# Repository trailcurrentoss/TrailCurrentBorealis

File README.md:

# TrailCurrent Borealis

Environmental and safety sensor node for toy haulers, RVs, and similar enclosed living spaces. Measures temperature, humidity, real CO2, VOC index, carbon monoxide, and propane / LPG levels, then broadcasts readings over a CAN bus. Supports over-the-air (OTA) firmware updates, WiFi credential provisioning via CAN, and network discovery for integration with TrailCurrent Headwaters.

## Hardware

- **MCU board:** [Waveshare ESP32-S3-RS485-CAN](https://www.waveshare.com/esp32-s3-rs485-can.htm)
  - ESP32-S3R8 (8MB PSRAM, external 16MB flash)
  - Built-in isolated CAN transceiver (TJA1051) on GPIO15/16
  - Built-in isolated RS485 transceiver (unused by Borealis)
  - External PCF85063AT RTC
  - 7-36V DC input or 5V USB-C
- **CO2 / temp / humidity:** DFRobot SEN0536 (Sensirion SCD41, photoacoustic NDIR)
- **VOC trending:** DFRobot SEN0394 (Sensirion SGP40, VOC Index 1-500)
- **Carbon monoxide:** DFRobot SEN0466 (factory-calibrated electrochemical, 0-1000 ppm)
- **Propane / LPG:** DFRobot SEN0131 (MQ-6 with adjustable potentiometer)

### Pin Assignments

| GPIO | Function |
|------|----------|
| 5 | I2C SDA (SCD41, SGP40, SEN0466) |
| 6 | I2C SCL (SCD41, SGP40, SEN0466) |
| 3 | MQ-6 analog input (ADC1_CH2, via 10k/15k divider) |
| 15 | CAN TX (internal transceiver) |
| 16 | CAN RX (internal transceiver) |

See [`DOCS/sensor-wiring.md`](DOCS/sensor-wiring.md) for full wiring details and the [ribbon-cable diagram](DOCS/borealis-ribbon-cable.svg). When the parts arrive, work through [`DOCS/arrival-todos.md`](DOCS/arrival-todos.md) for the assembly, calibration, and validation checklist.

### Circuit Notes

- KiCad schematic and PCB files are in the `EDA/` directory
- The MQ-6 sensor's analog output swings 0-5V; a 10kΩ + 15kΩ resistor divider scales it to 0-3V at the ADC pin
- Add a 100nF cap from the ADC pin to GND for noise filtering near the heater

## Building

This project uses [ESP-IDF](https://docs.espressif.com/projects/esp-idf/en/stable/esp32s3/get-started/index.html) (v5.x).

```bash
# Configure (first time only)
idf.py set-target esp32s3

# Build
idf.py build

# Flash via USB
idf.py flash

# Monitor serial output
idf.py monitor

# Build, flash, and monitor in one step
idf.py build flash monitor
```

### OTA Upload

```bash
curl -X POST http://<hostname>.local/ota --data-binary @build/borealis.bin
```

## Architecture

| File | Purpose |
|------|---------|
| `main/main.c` | Sensor reading loop, TWAI task, CAN frame transmission |
| `main/sensors.c/h` | I²C drivers for SCD41, SGP40, SEN0466; ADC reading and Rs/R0 calculation for MQ-6 |
| `main/wifi_config.c/h` | NVS-backed WiFi credentials and STA connect/disconnect |
| `main/ota.c/h` | HTTP POST `/ota` server, runs in dedicated task |
| `main/discovery.c/h` | mDNS-based network discovery for Headwaters registration |

### CAN Bus Task

The TWAI (CAN) driver runs in a dedicated FreeRTOS task with alert-based message handling. It uses a dual-state transmission model:

- **TX_ACTIVE** (1000 ms period): Normal operation when peers are detected on the bus
- **TX_PROBING** (2000 ms period): Slow probe when no peers are ACKing, reduces bus noise

The task automatically transitions between states based on TX success/failure and incoming messages. Bus-off recovery is handled via TWAI alerts. This pattern is shared with all other TrailCurrent ESP-IDF modules — see `TrailCurrentReservoir`, `TrailCurrentSwitchback`, etc.

## CAN Bus Protocol

All communication uses a 500 kbps CAN bus. The device transmits sensor data and receives OTA / WiFi / discovery commands.

### Environmental Data (TX)

**CAN ID:** `0x1F` | **DLC:** 8 | **Period:** 1000 ms

| Byte | Content |
|------|---------|
| 0 | Temperature (°C, signed int8, rounded) |
| 1 | Temperature (°F, signed int8, rounded) |
| 2-3 | Humidity (big-endian uint16, value × 100, e.g. 4523 = 45.23%) |
| 4-5 | Real CO2 in ppm (big-endian uint16, NDIR measurement from SCD41) |
| 6-7 | VOC Index (big-endian uint16, range 1-500, baseline ≈ 100) |

### Safety Data (TX)

**CAN ID:** `0x20` | **DLC:** 8 | **Period:** 1000 ms

| Byte | Content |
|------|---------|
| 0-1 | CO concentration in ppm (big-endian uint16) |
| 2-3 | LPG / propane Rs/R0 ratio × 1000 (big-endian uint16; lower = more gas) |
| 4 | Alarm flags (bitmask) |
| 5-7 | Reserved |

Alarm flag bits:
- `0x01` CO warning (≥ 70 ppm)
- `0x02` CO alarm (≥ 200 ppm)
- `0x04` LPG warning (Rs/R0 < 0.5)
- `0x08` LPG alarm (Rs/R0 < 0.3)
- `0x10` CO2 warning (≥ 1500 ppm)
- `0x20` CO2 alarm (≥ 2500 ppm)
- `0x40` VOC alarm (Index ≥ 400)

### OTA Trigger (RX)

**CAN ID:** `0x00` | **DLC:** 3+

| Byte | Content |
|------|---------|
| 0-2 | Target MAC suffix (e.g., `F2 7E 6C` for hostname `esp32-F27E6C`) |

When the MAC matches, the device connects to its configured WiFi network, starts an HTTP server at `/ota`, and waits for a firmware upload for 3 minutes before returning to normal operation.

### WiFi Configuration (RX)

**CAN ID:** `0x01` | **DLC:** varies

WiFi credentials are provisioned over CAN using a chunked protocol. Credentials are stored in NVS (non-volatile storage) and persist across reboots.

| Byte 0 | Message Type |
|--------|-------------|
| `0x01` | Start: contains SSID length, password length, chunk counts |
| `0x02` | SSID chunk: 6-byte payload with chunk index |
| `0x03` | Password chunk: 6-byte payload with chunk index |
| `0x04` | End: contains XOR checksum for validation |

The protocol includes a 5-second timeout — if chunks stop arriving, the state resets.

### Discovery Trigger (RX)

**CAN ID:** `0x02` | **DLC:** any (broadcast)

When received, the device connects to WiFi and advertises itself via mDNS (`_trailcurrent._tcp`) with TXT records:

| Key | Value |
|-----|-------|
| `type` | `borealis` |
| `canid` | `0x1F` |
| `fw` | firmware version |

Headwaters confirms registration by calling `GET /discovery/confirm`. The discovery window is 3 minutes.

### Firmware Version Report (TX)

**CAN ID:** `0x04` | **DLC:** 6

Sent once on boot after CAN initialization, then again whenever a peer is first detected. Reports the running firmware version so Headwaters can track what each device is running.

| Byte | Content |
|------|---------|
| 0-2 | Last 3 bytes of device WiFi MAC (matches hostname `esp32-XXYYZZ`) |
| 3 | Version major |
| 4 | Version minor |
| 5 | Version patch |

## Air Quality and Safety Thresholds

### Real CO2 (SCD41, NDIR)

| ppm | Level |
|-----|-------|
| < 800 | Fresh / well-ventilated |
| 800-1499 | Normal indoor |
| 1500-2499 | Stuffy / drowsiness possible |
| ≥ 2500 | Alarm |

### VOC Index (SGP40)

| Index | Meaning |
|-------|---------|
| 1-99 | Better than recent baseline |
| 100 | Typical indoor air (24-hour running average) |
| 101-249 | Worse than baseline |
| 250-399 | Significant pollution event |
| 400-500 | Severe pollution event |

### Carbon Monoxide (SEN0466)

| ppm | Level |
|-----|-------|
| < 35 | Normal |
| 35-69 | Elevated |
| 70-199 | Warning |
| ≥ 200 | Alarm |

### Propane / LPG (MQ-6, Rs/R0 ratio)

| Rs/R0 | Level |
|-------|-------|
| > 0.7 | Clean air |
| 0.5-0.7 | Trace |
| 0.3-0.5 | Warning |
| < 0.3 | Alarm |

The MQ-6 outputs a resistance ratio rather than ppm; calibrating to absolute ppm requires tank-test exposure. For leak detection the ratio is what matters: a sharp drop from baseline indicates propane present.

## OTA Updates

1. Provision WiFi credentials via CAN (one-time setup, stored in NVS)
2. Send an OTA trigger message on CAN ID `0x00` with the target device's MAC suffix
3. The device connects to WiFi
4. Upload firmware via HTTP: `curl -X POST http://<hostname>.local/ota --data-binary @build/borealis.bin`
5. On success, the device reboots with new firmware
6. On timeout (3 minutes), the device disconnects WiFi and resumes normal operation

The device hostname is printed to serial at boot (format: `esp32-XXYYZZ`).

## License

[MIT](LICENSE)

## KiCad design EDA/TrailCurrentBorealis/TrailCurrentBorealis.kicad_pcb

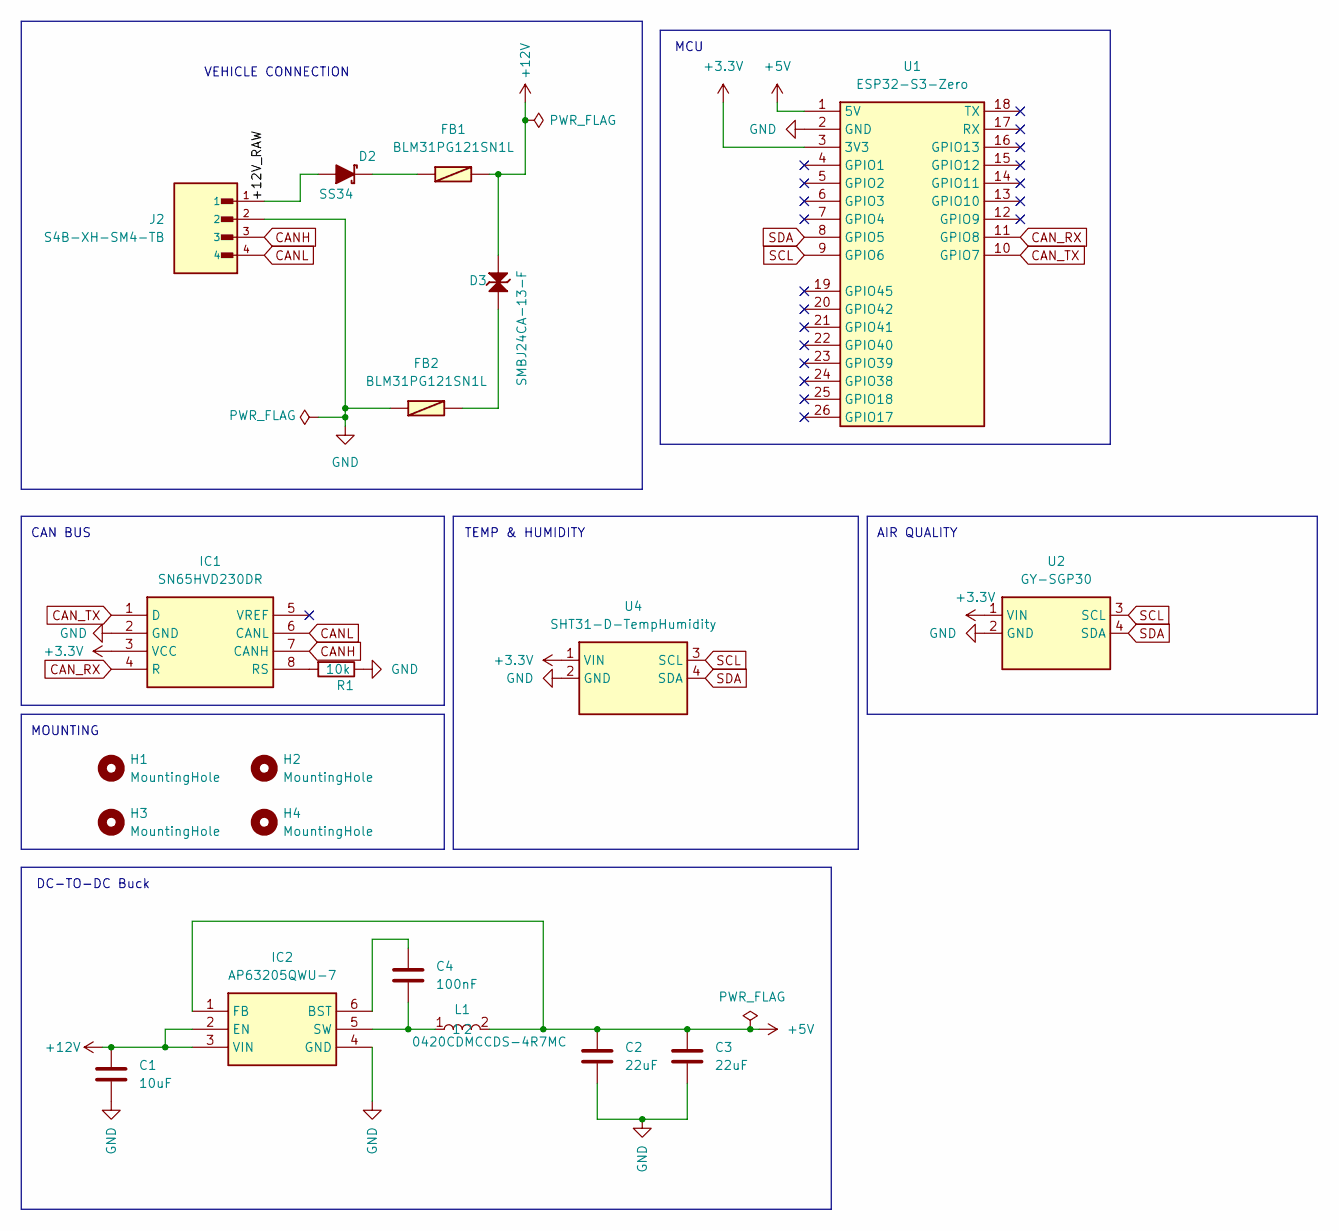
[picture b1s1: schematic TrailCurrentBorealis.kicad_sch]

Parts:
C1: 10uF; C_1206_3216Metric_Pad1.33x1.80mm_HandSolder
C2, C3: 22uF; C_1206_3216Metric_Pad1.33x1.80mm_HandSolder
C4: 100nF; C_1206_3216Metric_Pad1.33x1.80mm_HandSolder
D2: SS34; Manufacturer_Part_Number SS34; LCSC Part C8678
D3: SMBJ24CA-13-F; Manufacturer_Part_Number SMBJ24CA; LCSC Part C83268
FB1, FB2: BLM31PG121SN1L; Manufacturer_Part_Number BLM31PG121SN1L; LCSC Part C85841
H1, H2, H3, H4: MountingHole; MountingHole_2.5mm
IC1: SN65HVD230DR; Mouser Part Number 595-SN65HVD230DR
IC2: AP63205QWU-7; AP63205QWU7; Manufacturer_Part_Number AP63205QWU-7; LCSC Part C5248537
J2: S4B-XH-SM4-TB; JST_S4B-XH-SM4-TB; LCSC Part C161861
L1: 0420CDMCCDS-4R7MC; Manufacturer_Part_Number 0420CDMCCDS-4R7MC; LCSC Part C2638679
R1: 10k; R_1206_3216Metric_Pad1.30x1.75mm_HandSolder
U1: ESP32-S3-Zero; ESP32-S3-Zero_SMD; Manufacturer_Part_Number ESP32-S3-Zero
U2: GY-SGP30
U4: SHT31-D-TempHumidity

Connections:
+3.3V: IC1.3 (VCC), U1.3 (3V3), U2.1 (VIN), U4.1 (VIN)
+5V: C2.1, C3.1, IC2.1 (FB), L1.2, U1.1 (5V)
+12V: C1.1, D3.2, FB1.2, IC2.2 (EN), IC2.3 (VIN)
/+12V_RAW: D2.2 (A), J2.1
CANH: IC1.7 (CANH), J2.3
CANL: IC1.6 (CANL), J2.4
CAN_RX: IC1.4 (R), U1.11 (GPIO8)
CAN_TX: IC1.1 (D), U1.10 (GPIO7)
GND: C1.2, C2.2, C3.2, FB2.1, IC1.2 (GND), IC2.4 (GND), J2.2, R1.1, U1.2 (GND), U2.2 (GND), U4.2 (GND)
unnamed: D2.1 (K), FB1.1
unnamed: D3.1, FB2.2
unnamed: IC1.8 (RS), R1.2
unnamed: C4.1, IC2.6 (BST)
unnamed: C4.2, IC2.5 (SW), L1.1
SCL: U1.9 (GPIO6), U2.3 (SCL), U4.3 (SCL)
SDA: U1.8 (GPIO5), U2.4 (SDA), U4.4 (SDA)

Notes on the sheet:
VEHICLE CONNECTION
DC-TO-DC Buck
AIR QUALITY
MOUNTING
MCU
CAN BUS
TEMP & HUMIDITY

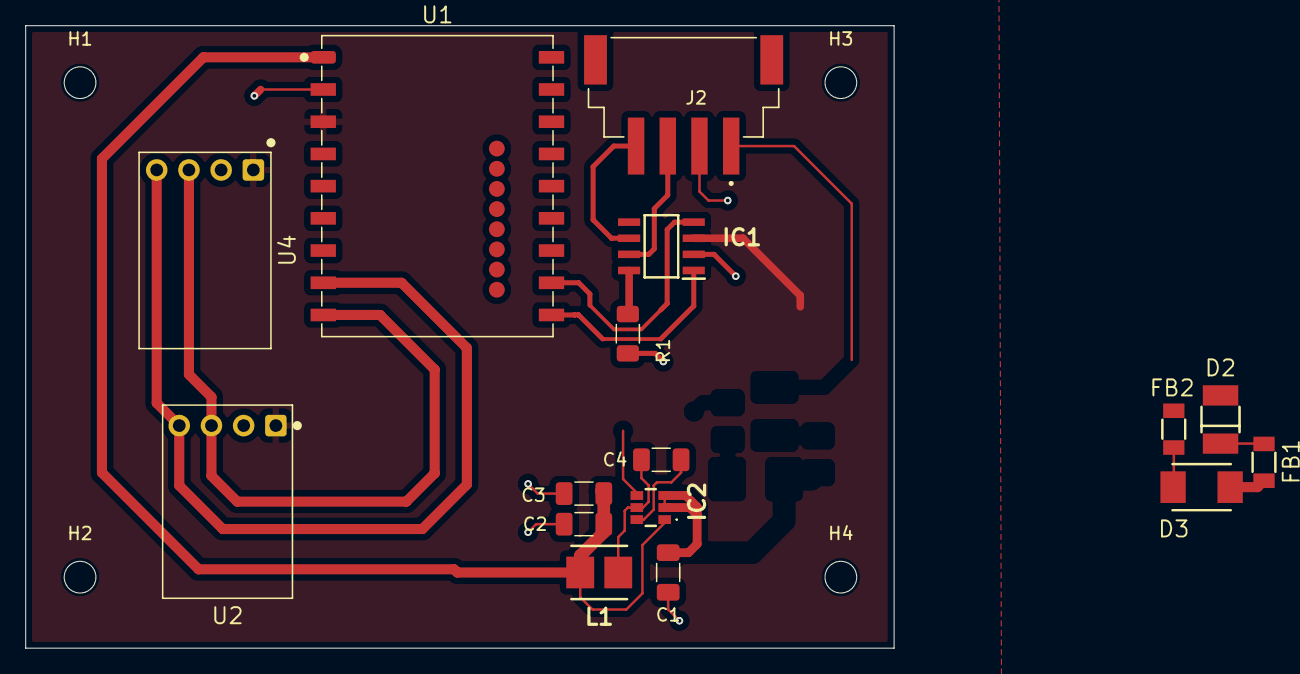
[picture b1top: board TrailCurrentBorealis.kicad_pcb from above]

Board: 2 copper layers, 68.5 x 49.1 mm, 22 parts (1 on the bottom side), 16 nets.

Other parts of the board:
LOGO: TrailCurrentLogo_Text
LOGO#2: TrailCurrentLogo_Icon

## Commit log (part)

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2026-03-07 Starting Borealis project
2026-03-07 Adding license
2026-03-07 Adding readme
2026-03-07 Fixes for connecting to wifi and accepting OTA message
2026-03-07 Temp offset fix for DHT22
2026-03-12 CAD for milling PCB on Genmistu 3030 just edges and drill holes not tracks
2026-03-12 Milling success, saving changes
2026-03-12 EDA in progrss for DIY board, single sided traces for early etching examples pior to ordering
2026-03-17 Switching to new temp and humdity sensor
2026-03-17 Updated PCB for DIY build
2026-03-17 One additional footprint change for DIY board
2026-03-17 Ready for DIY manufacturing
2026-03-17 Fixed pin assignments to align with EDA
2026-03-17 Working state with DIY board. Will revise with Mfg board soon.
2026-03-17 Disabling debug for produciton deployment
2026-03-18 Revised version of the case design. Grbls added for mfg
2026-03-19 WIP EDA advancing the PCB further with better buck converter and reverse polarity protection
2026-03-27 Migrated to ESP-IDF
2026-03-27 Implementing temp offset coming from headwaters
2026-03-28 Fixed bug where discovery would disrupt CAN messaging
2026-03-28 Aligned OTA and Discovery with Switchback
2026-03-28 Fixing issue with CAN Bus stops responding when discovery happens
2026-03-28 Fixed bug with init that was causing TWAI not to send / receive
2026-03-29 Changes to provide version on OTA
2026-04-12 Adding discovery for this device
2026-05-04 Moving to new ESP32S3 and new sensors to provider broader range of coverage for air quality measurements.
2026-05-04 Adding todos for when the sensors arrive
2026-05-04 Optimizations to get accurate readings and alarms
